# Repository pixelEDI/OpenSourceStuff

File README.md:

# Projekte, Links und Dokus zu Open-Source Projekten und Videos

Have fun | https://links.pixelEDI.eu

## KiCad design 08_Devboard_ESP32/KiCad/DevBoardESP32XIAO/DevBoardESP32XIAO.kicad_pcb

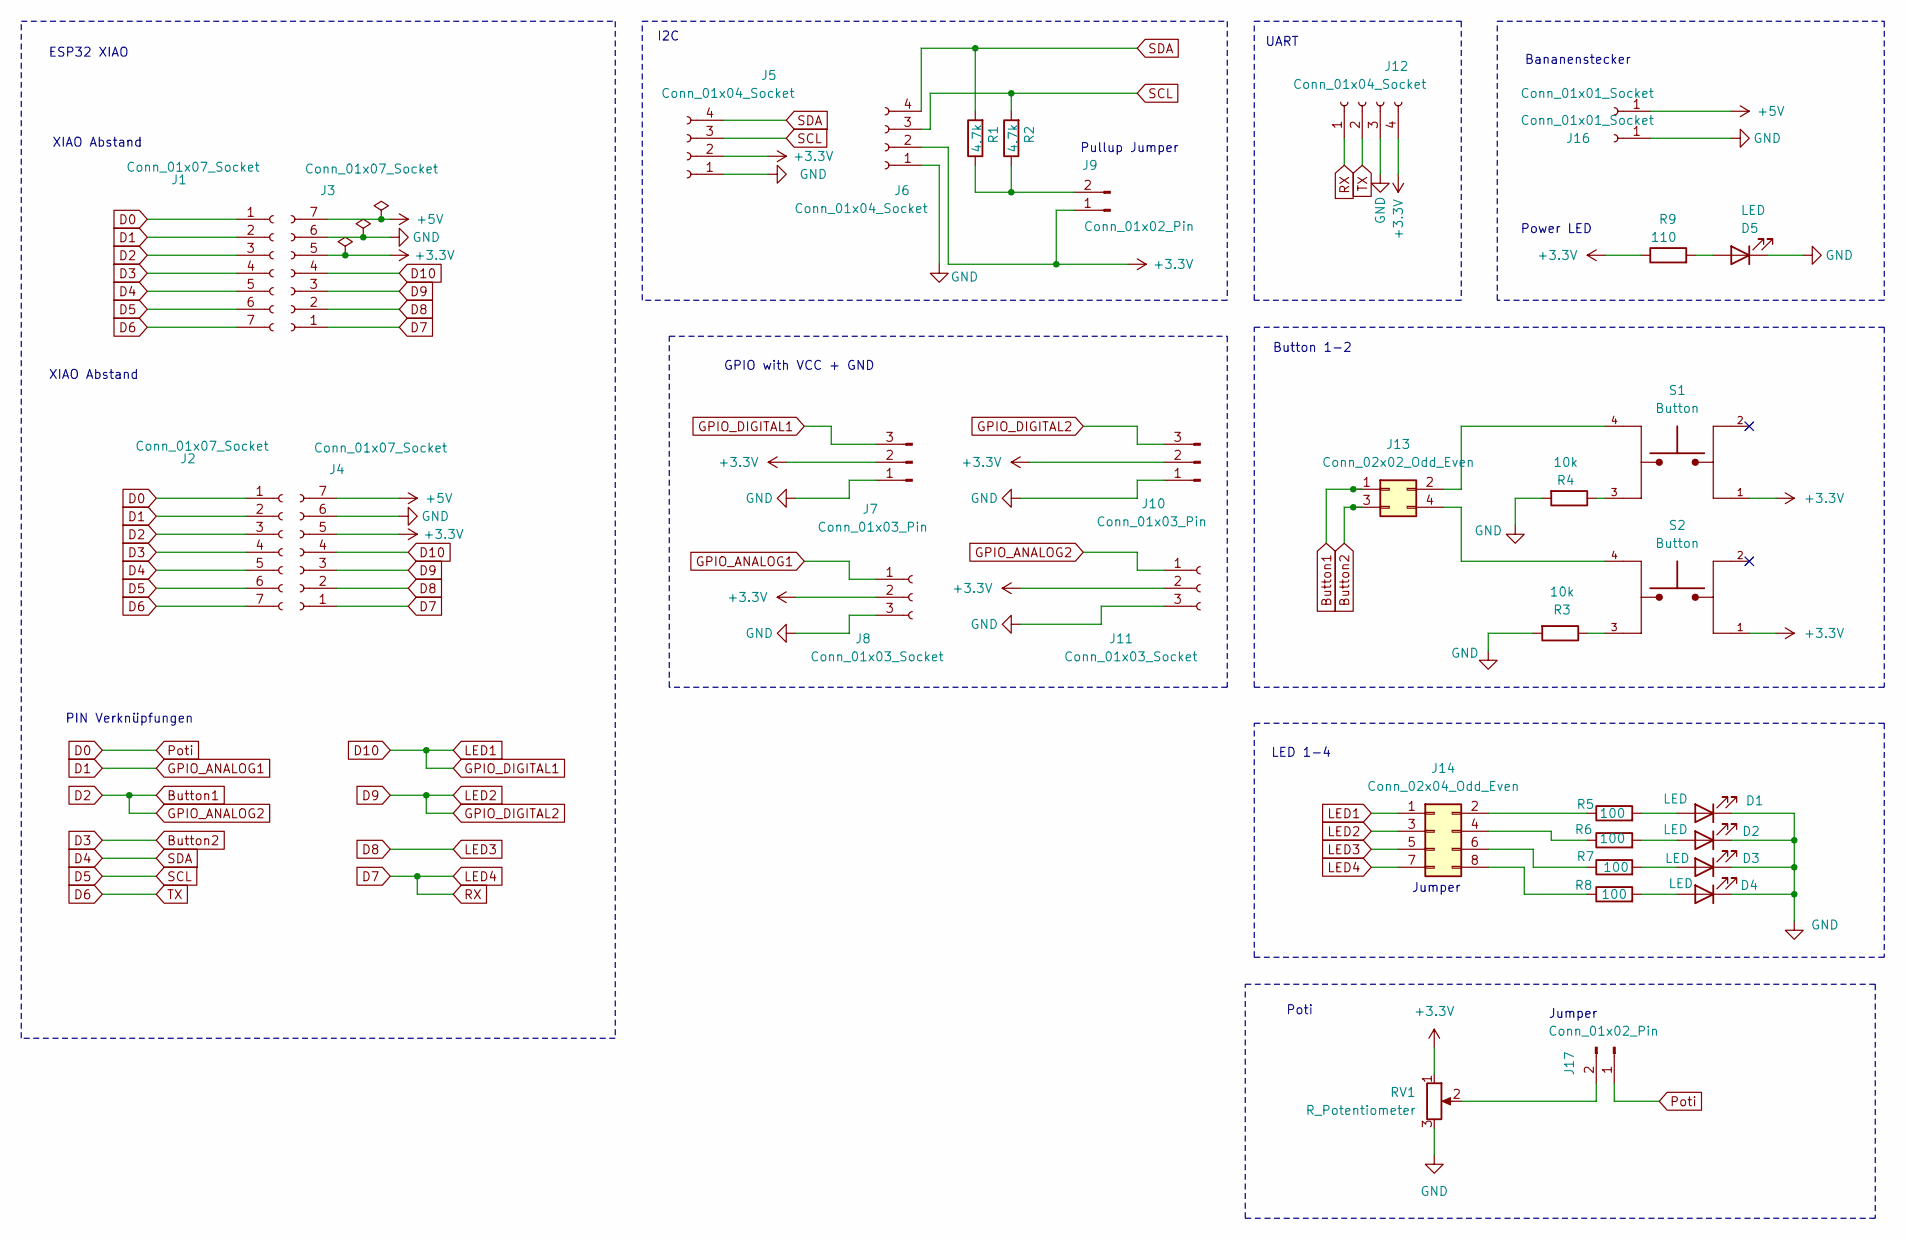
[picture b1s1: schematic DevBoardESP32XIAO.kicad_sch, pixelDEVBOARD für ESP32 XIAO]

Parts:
D1, D2, D3, D4, D5: LED; LED_0805_2012Metric
J1, J2, J3, J4: Conn_01x07_Socket; PinSocket_1x07_P2.54mm_Vertical
J5, J12: Conn_01x04_Socket; PinSocket_1x04_P2.54mm_Vertical
J6: Conn_01x04_Socket; PinHeader_1x04_P2.54mm_Vertical
J7, J10: Conn_01x03_Pin; PinHeader_1x03_P2.54mm_Vertical
J8, J11: Conn_01x03_Socket; PinSocket_1x03_P2.54mm_Vertical
J9, J17: Conn_01x02_Pin; PinHeader_1x02_P2.54mm_Vertical
J13: Conn_02x02_Odd_Even; PinHeader_2x02_P2.54mm_Vertical
J14: Conn_02x04_Odd_Even; PinHeader_2x04_P2.54mm_Vertical
J15, J16: Conn_01x01_Socket; Banana_Jack_1Pin
R1, R2: 4.7k; R_0805_2012Metric
R3, R4: 10k; R_0805_2012Metric
R5, R6, R7, R8: 100; R_0805_2012Metric
R9: 110; R_0805_2012Metric
RV1: R_Potentiometer; Potentiometer_Alps_RK09K_Single_Vertical
S1, S2: Button; SW_TL3305AF160QG; PARTREV C

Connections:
+3.3V: J3.5, J4.5, J5.2, J6.2, J7.2, J8.2, J9.1, J10.2, J11.2, J12.4, R9.1, RV1.1, S1.1, S2.1
+5V: J3.7, J4.7, J15.1
Button1: J1.3, J2.3, J11.1, J13.1
Button2: J1.4, J2.4, J13.3
D0: J1.1, J2.1, J17.1
D1: J1.2, J2.2, J8.1
D4: J1.5, J2.5, J5.4, J6.4, R1.2
D5: J1.6, J2.6, J5.3, J6.3, R2.2
D6: J1.7, J2.7, J12.2
D7: J3.1, J4.1, J12.1, J14.7
D8: J3.2, J4.2, J14.5
D9: J3.3, J4.3, J10.3, J14.3
D10: J3.4, J4.4, J7.3, J14.1
GND: D1.1 (K), D2.1 (K), D3.1 (K), D4.1 (K), D5.1 (K), J3.6, J4.6, J5.1, J6.1, J7.1, J8.3, J10.1, J11.3, J12.3, J16.1, R3.2, R4.2, RV1.3
unnamed: D1.2 (A), R5.2
unnamed: D2.2 (A), R6.2
unnamed: D3.2 (A), R7.2
unnamed: D4.2 (A), R8.2
unnamed: D5.2 (A), R9.2
unnamed: J9.2, R1.1, R2.1
unnamed: J13.2, S1.4
unnamed: J13.4, S2.4
unnamed: J14.2, R5.1
unnamed: J14.4, R6.1
unnamed: J14.6, R7.1
unnamed: J14.8, R8.1
unnamed: J17.2, RV1.2
unnamed: R3.1, S2.3
unnamed: R4.1, S1.3

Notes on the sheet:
PIN Verknüpfungen
Poti
LED 1-4
ESP32 XIAO
UART
Pullup Jumper
I2C
XIAO Abstand
Bananenstecker
GPIO with VCC + GND
Jumper
Power LED
Button 1-2

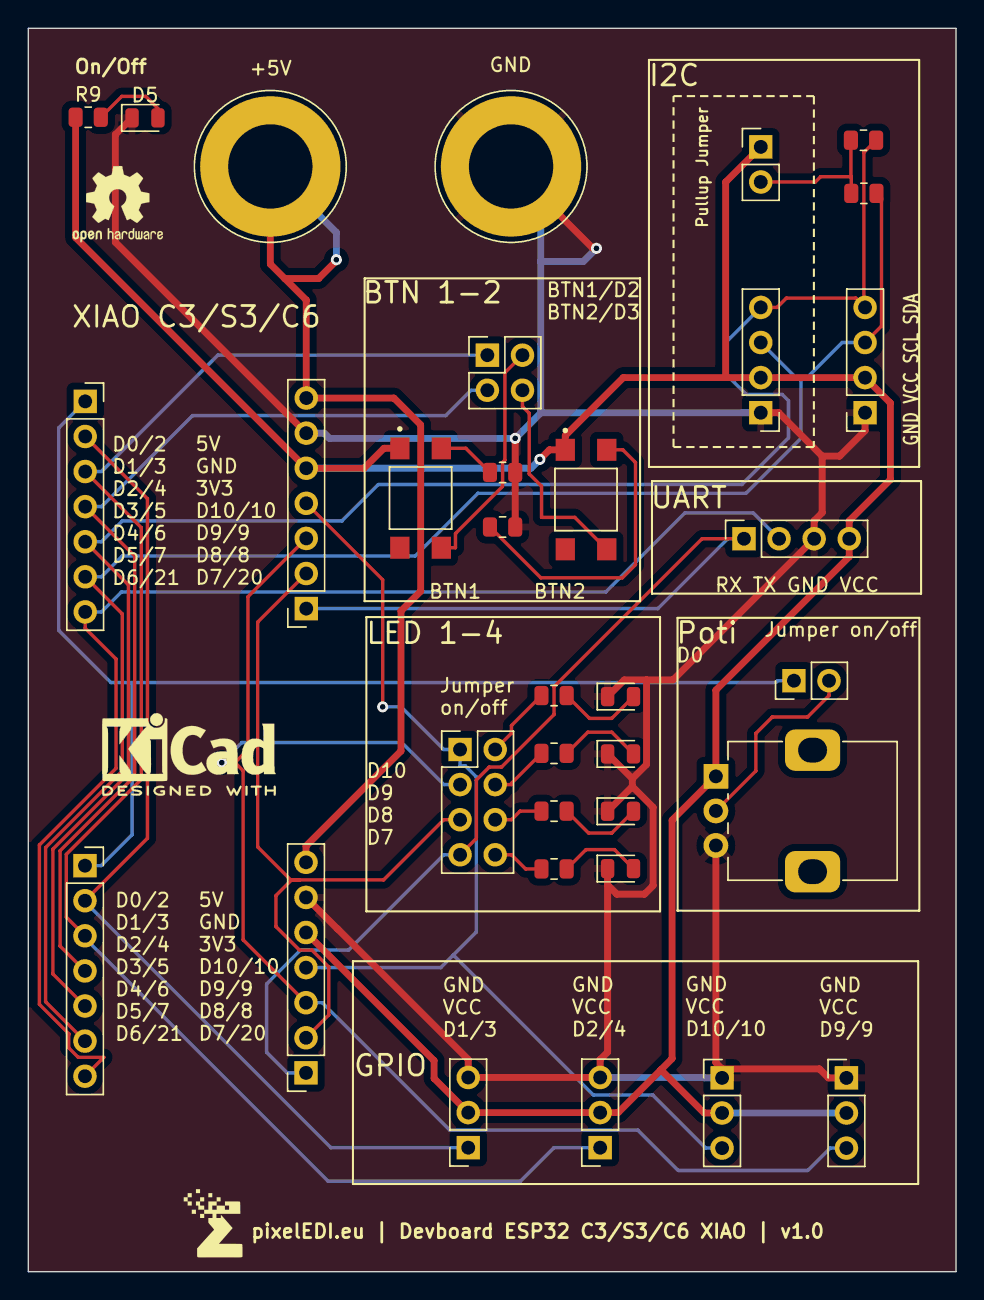
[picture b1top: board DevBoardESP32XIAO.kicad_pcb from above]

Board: 2 copper layers, 67.1 x 90.0 mm, 34 parts (0 on the bottom side), 29 nets.

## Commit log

2024-05-21 gpt4all
2024-05-21 readme licence
2024-06-04 darktheme nodered
2024-06-04 Node-RED link beispiel
2024-06-04 partdb installation
2024-06-04 vserver 2024
2024-06-18 SimulIDE beispiel
2024-07-16 apache answer
2024-08-02 esp32 prototyping devboard
2024-08-15 arduino uno debugging
2024-08-19 platformio start
2024-09-03 nodered projects§
2024-09-03 Markdown Mermaid
2024-09-10 SimulIDE
2024-09-10 simulide doppelter eintrag
2024-10-11 Nextcloud Hub9 update und Whiteboard
2024-11-11 selfhosted list 2024
2024-11-11 Linkliste OpenSource Fragmentierung
2024-12-08 Bauteile und Schaltplan
2024-12-09 hugo website
2024-12-16 stow
2025-01-14 Arduino-Maker-Workshop example
2025-01-14 readme
2025-01-20 nextcloud api scripting
2025-02-11 Selfhosted Notizen: Memos
2025-02-11 Beispiel für Node-RED mit DIY Bearer Token
2025-02-11 nosqlexample
2025-02-20 ssh config
2025-02-20 Nextcloud AIO in 2025
2025-02-20 Nextcloud notizen via webdav mit rclone syncen
2025-02-20 Nextcloud tasks mit todoman via vdirsyncer
2025-03-11 termsofabuse
2025-03-17 Nextcloud Talk via CLI bzw bash script
2025-04-16 Open Source Mythen Linkliste
2025-06-24 Nextcloud Remote Backup Settings
2025-06-24 Node-RED debugging beispiele
2025-07-23 esp32_framework
2025-09-24 OfflineNavigation
2025-10-01 sudo setup mit fido2
2025-10-14 picokey bsp mit rp2350
2025-11-10 lopaka diy gui mit esp32 und ssd1306
2025-11-10 node-red .env bsp
2025-11-26 hardware keys
2026-01-05 1767601574
2026-01-13 llamacpp for linux
2026-01-22 Bruce-Firmware
2026-04-16 velxio lokale emulator fuer mcu
2026-04-16 missinglink
